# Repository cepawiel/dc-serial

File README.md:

# Dreamcast Serial Adapters

## [CP2102N Adapter](DCSDv2_CP2102N/README.md)
Replacement PCB for the Dreamcast SD to Serial adapters
that are available online. Intended to be used with [dcload-serial](https://github.com/KallistiOS/dcload-serial/) for development of homebrew.

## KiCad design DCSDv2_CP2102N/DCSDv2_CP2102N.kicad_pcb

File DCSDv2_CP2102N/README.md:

# CP2102N Adapter

## Info
This is a serial adapter designed around the CP2102N USB <-> Serial IC. 

On the PCB there's solder jumpers for connecting the clock and serial pins. I haven't experimented with using them yet, but that was the intention behind including them.

## Programing
By default the LEDs are not enabled, but can be using the [USBXpress]() software from Silicon Labs. Various other options include setting the Manufacturer & Product Strings. A [brief guide](https://www.silabs.com/documents/public/application-notes/AN721.pdf) to the tool is avaiable. To enable the LEDs make sure the "Alternate Function" for GPIO0 & 1 are set to the TX & RX Toggle options.

## Ordering
Files for ordering from JLCPCB are avaiable [here](jlcpcb/production_files/) including assembly files. I do usually select the option for them to double check the pick and place file since I believe I'm doing something incorrect with respect to the origin. In addition to the PCBs and components you'll need to procure a Dreamcast SD Adapter that are avaiable on Aliexpress/Ebay/Amazon ($10-$20) for the serial connector.

## Photos

## Changelog

### TODO
- Current PCB alignment holes are slightly too small. Using a 3/64" bit to widen holes allows for a pretty good fit.

### V1.1
- Swapped RX/TX & RTS/CTS
- Placed components on bottom to allow USB-C to fit without modifications to case

### V1.0
- Initial Order

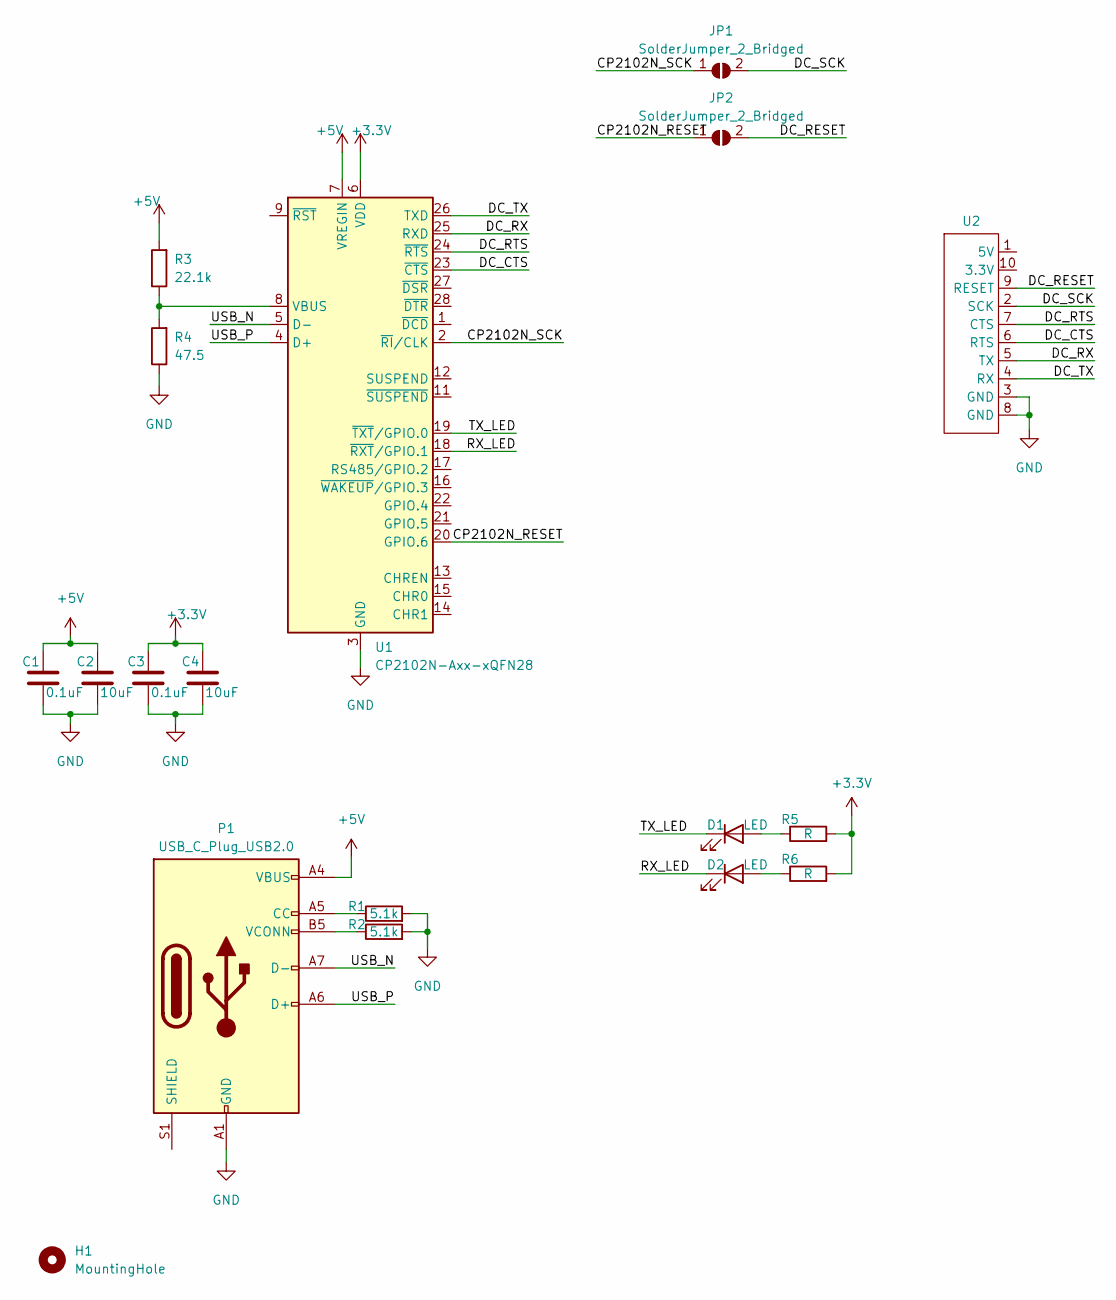
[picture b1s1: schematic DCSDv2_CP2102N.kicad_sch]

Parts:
C1, C3: 0.1uF; C_0402_1005Metric
C2, C4: 10uF; C_0402_1005Metric
D1, D2: LED; LED_0603_1608Metric
H1: MountingHole; DCSDv2
JP1, JP2: SolderJumper_2_Bridged; SolderJumper-2_P1.3mm_Open_RoundedPad1.0x1.5mm
P1: USB_C_Plug_USB2.0; USB_C_Receptacle_HRO_TYPE-C-31-M-12
R1, R2: 5.1k; R_0402_1005Metric
R3: 22.1k; R_0402_1005Metric
R4: 47.5; R_0402_1005Metric
R5, R6: R; R_0402_1005Metric
U1: CP2102N-Axx-xQFN28; QFN-28-1EP_5x5mm_P0.5mm_EP3.35x3.35mm
U2: DCSD_Serial

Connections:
+3.3V: C3.1, C4.1, R5.2, R6.2, U1.6 (VDD)
+5V: C1.1, C2.1, P1.A4 (VBUS), P1.A9 (VBUS), P1.B4 (VBUS), P1.B9 (VBUS), R3.2, U1.7 (VREGIN)
/CP2102N_RESET: JP2.1 (A), U1.20 (GPIO.6)
/CP2102N_SCK: JP1.1 (A), U1.2 (~RI/CLK)
/DC_CTS: U1.23 (~CTS), U2.6 (RTS)
/DC_RESET: JP2.2 (B), U2.9 (RESET)
/DC_RTS: U1.24 (~RTS), U2.7 (CTS)
/DC_RX: U1.25 (RXD), U2.5 (TX)
/DC_SCK: JP1.2 (B), U2.2 (SCK)
/DC_TX: U1.26 (TXD), U2.4 (RX)
/RX_LED: D2.1 (K), U1.18 (~RXT/GPIO.1)
/TX_LED: D1.1 (K), U1.19 (~TXT/GPIO.0)
/USB_N: P1.A7 (D-), P1.B7 (D-), U1.5 (D-)
/USB_P: P1.A6 (D+), P1.B6 (D+), U1.4 (D+)
GND: C1.2, C2.2, C3.2, C4.2, P1.A1 (GND), P1.A12 (GND), P1.B1 (GND), P1.B12 (GND), R1.2, R2.2, R4.1, U1.3 (GND), U1.29 (GND), U2.3 (GND), U2.8 (GND)
unnamed: D1.2 (A), R5.1
unnamed: D2.2 (A), R6.1
unnamed: P1.A5 (CC), R1.1
unnamed: P1.B5 (VCONN), R2.1
unnamed: R3.1, R4.2, U1.8 (VBUS)

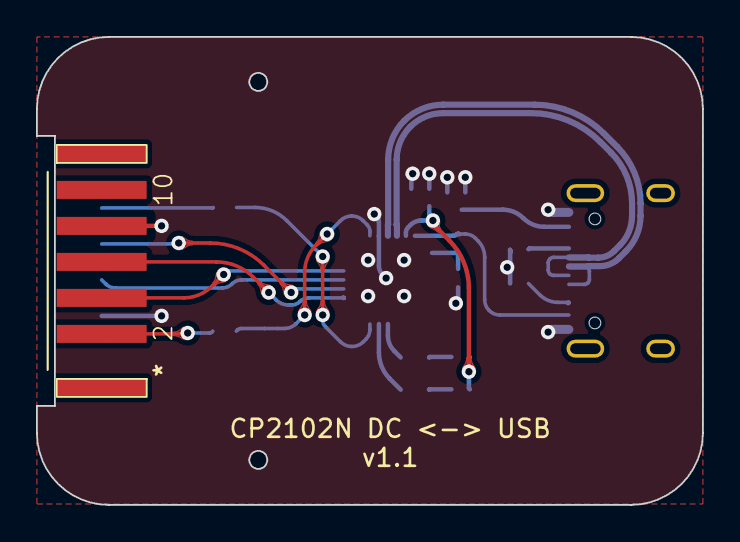
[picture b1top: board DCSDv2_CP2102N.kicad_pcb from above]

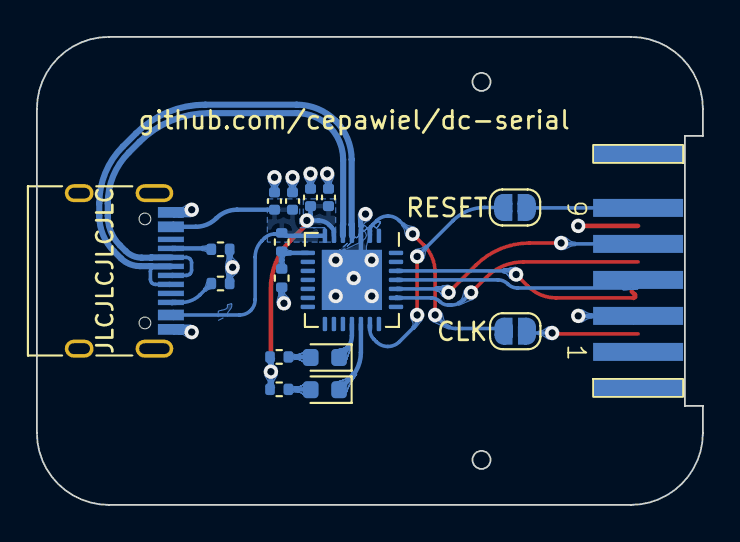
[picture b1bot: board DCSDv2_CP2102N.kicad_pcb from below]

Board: 2 copper layers, 37.0 x 26.0 mm, 18 parts (17 on the bottom side), 20 nets.

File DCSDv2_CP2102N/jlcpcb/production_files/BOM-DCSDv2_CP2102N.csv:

Comment,Designator,Footprint,LCSC
0.1uF,"C1,C3",C_0402_1005Metric,C1525
10uF,"C2,C4",C_0402_1005Metric,C15525
USB_C_Plug_USB2.0,P1,USB_C_Receptacle_HRO_TYPE-C-31-M-12,C165948
LED,D1,LED_0603_1608Metric,C2286
LED,D2,LED_0603_1608Metric,C2290
R,"R5,R6",R_0402_1005Metric,C25133
22.1k,R3,R_0402_1005Metric,C25765
47.5,R4,R_0402_1005Metric,C25792
5.1k,"R1,R2",R_0402_1005Metric,C25905
CP2102N-Axx-xQFN28,U1,QFN-28-1EP_5x5mm_P0.5mm_EP3.35x3.35mm,C964632
~,U2,DCSD_Serial,

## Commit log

2023-07-17 First PCB Order
2023-07-31 Version 1.1
2023-07-31 Add READMEs with images
